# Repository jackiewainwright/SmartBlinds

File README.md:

# SmartBlinds
A senior design project that has a mobile application that sends user preferences (time, light, temp) to a micro controller system. The micro controller system tells the blinds whether to go up or down based off input from the sensor subsystem. The micro controller controls the motors which raises blinds up/down and opens slats.

# Motors
File descriptions:
- motorhw: is an Eagle project that contains the PCB I printed. The PCB was only half used since it was printed before we switched motors. The half containing the Nano and transceiver is used, while the half containing motor drivers is unused. Pictures of the schematic and layouts are in motorhw\_schematic.png and motorhw\_layout.png. 
- hardware\_photo.jpg and switch\_photo.jpg: Pictures of the final products.
- motor\_demonstration.mov: Video of the blinds being lifted, lowered and rotated to their limits. 
- logic\_diagram.png and power\_diagram.png: Basic schematics made in Fritzing. These are kind of low-quality because I couldn't find files for every part. In the logic diagram, two jacks are shown; the top supplies 12V and the bottom supplies 5V. In the drivers, A1,A2,B1,B2 aren't connected; they each should be connected to a motor. In the power diagram, imagine the battery is a Li-Ion, replace the TP4056 with a TP5410, imagine it's on a protoboard instead of breadboard. 
- keiths\_program.ino: Program used by Keith on the nano. 
- my\_program.ino: Program used by me to develop and test the motor subsystem.
- additional_validation.pdf: Validation that I didn't put in the report. My bad

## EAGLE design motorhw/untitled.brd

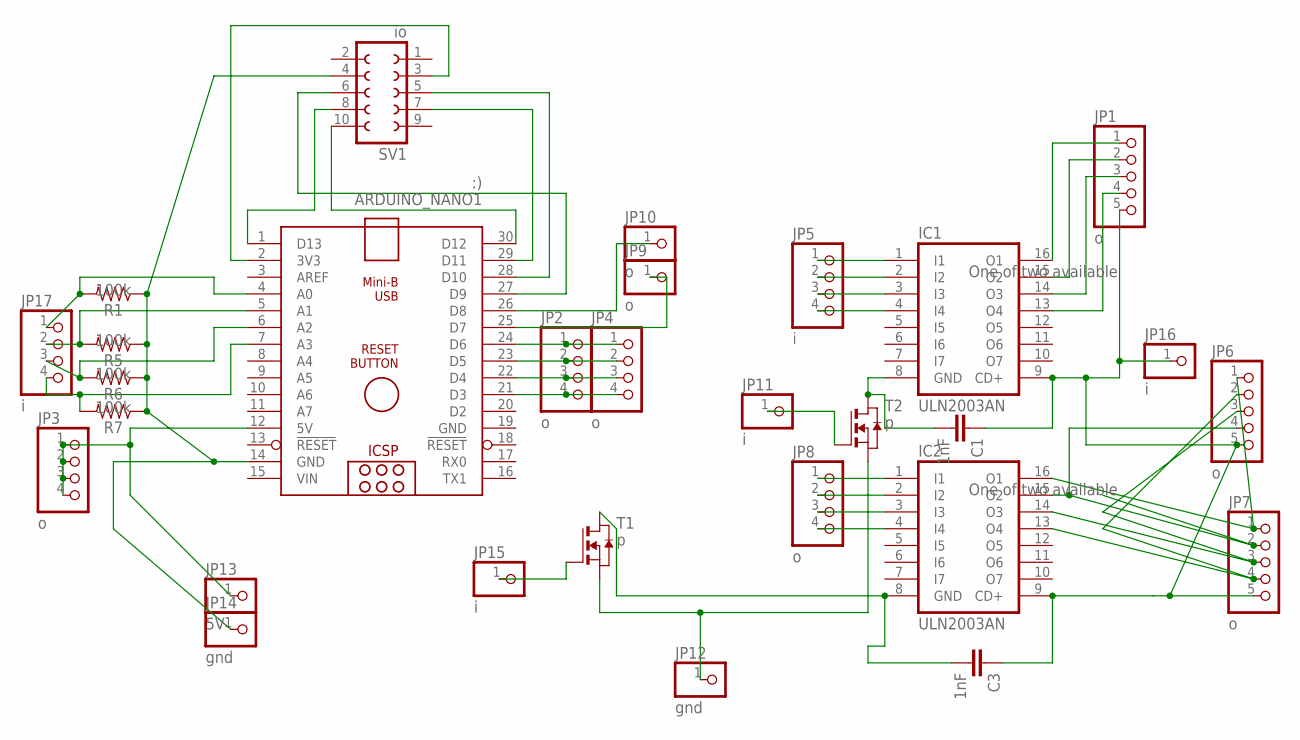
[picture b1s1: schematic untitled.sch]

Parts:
ARDUINO_NANO1: :); ARDUINO_NANO
C1, C3: 1nF; 0603
IC1, IC2: ULN2003AN; DIL16
JP1, JP6, JP7: o; 1X05
JP2, JP3, JP4, JP8: o; 1X04
JP5, JP17: i; 1X04
JP9, JP10: o; 1X01
JP11, JP15, JP16: i; 1X01
JP12, JP14: gnd; 1X01
JP13: 5V; 1X01
R1, R5, R6, R7: 100k; 0603
SV1: io; FE05-2
T1, T2: p; SOT89

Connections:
3V3: ARDUINO_NANO1.1 (D13), SV1.8
GND: ARDUINO_NANO1.19 (GND)
GND1: ARDUINO_NANO1.14 (GND), JP14.1, R1.1, R5.1, R6.1, R7.1, SV1.4
GND2: JP12.1, T1.3 (S), T2.3 (S)
LONGTHINGY: IC2.15 (O2), JP6.4, JP7.2
unnamed: ARDUINO_NANO1.4 (A0), JP17.1, R1.2
unnamed: ARDUINO_NANO1.21 (D3), JP2.4, JP4.4
unnamed: ARDUINO_NANO1.30 (D12), SV1.10
unnamed: IC2.16 (O1), JP6.1, JP7.1
unnamed: IC2.14 (O3), JP6.3, JP7.3
unnamed: IC2.13 (O4), JP6.2, JP7.4
unnamed: IC1.16 (O1), JP1.1
unnamed: IC1.15 (O2), JP1.2
unnamed: IC1.14 (O3), JP1.3
unnamed: IC1.13 (O4), JP1.4
unnamed: ARDUINO_NANO1.22 (D4), JP2.3, JP4.3
unnamed: ARDUINO_NANO1.25 (D7), JP9.1
unnamed: ARDUINO_NANO1.23 (D5), JP2.2, JP4.2
unnamed: ARDUINO_NANO1.29 (D11), SV1.7
unnamed: ARDUINO_NANO1.28 (D10), SV1.5
unnamed: ARDUINO_NANO1.27 (D9), SV1.6
unnamed: ARDUINO_NANO1.24 (D6), JP2.1, JP4.1
unnamed: ARDUINO_NANO1.2 (3V3), SV1.3
unnamed: IC1.1 (I1), JP5.1
unnamed: IC1.2 (I2), JP5.2
unnamed: IC1.3 (I3), JP5.3
unnamed: IC1.4 (I4), JP5.4
unnamed: IC2.1 (I1), JP8.1
unnamed: IC2.2 (I2), JP8.2
unnamed: IC2.3 (I3), JP8.3
unnamed: IC2.4 (I4), JP8.4
unnamed: ARDUINO_NANO1.26 (D8), JP10.1
unnamed: JP11.1, T2.1 (G)
unnamed: JP15.1, T1.1 (G)
unnamed: ARDUINO_NANO1.5 (A1), JP17.2, R5.2
unnamed: ARDUINO_NANO1.6 (A2), JP17.3, R6.2
unnamed: ARDUINO_NANO1.7 (A3), JP17.4, R7.2
ULN1GND: C1.2, IC1.8 (GND), T2.2 (D), T2.2@1 (D)
ULN2GND: C3.2, IC2.8 (GND), T1.2 (D), T1.2@1 (D)
VCC1: ARDUINO_NANO1.12 (5V), JP3.1, JP3.2, JP3.3, JP3.4, JP13.1
VCC2: C1.1, C3.1, IC1.9 (CD+), IC2.9 (CD+), JP1.5, JP6.5, JP7.5, JP16.1
VIN: ARDUINO_NANO1.15 (VIN)

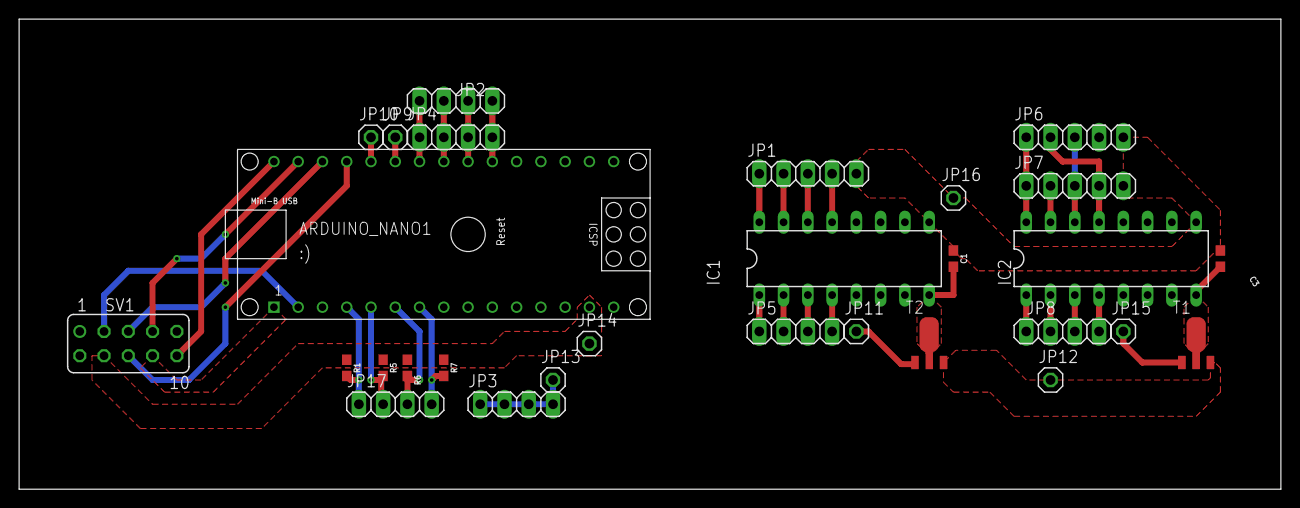
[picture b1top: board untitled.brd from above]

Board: 2 copper layers, 132.1 x 49.2 mm, 29 parts (0 on the bottom side), 40 nets.

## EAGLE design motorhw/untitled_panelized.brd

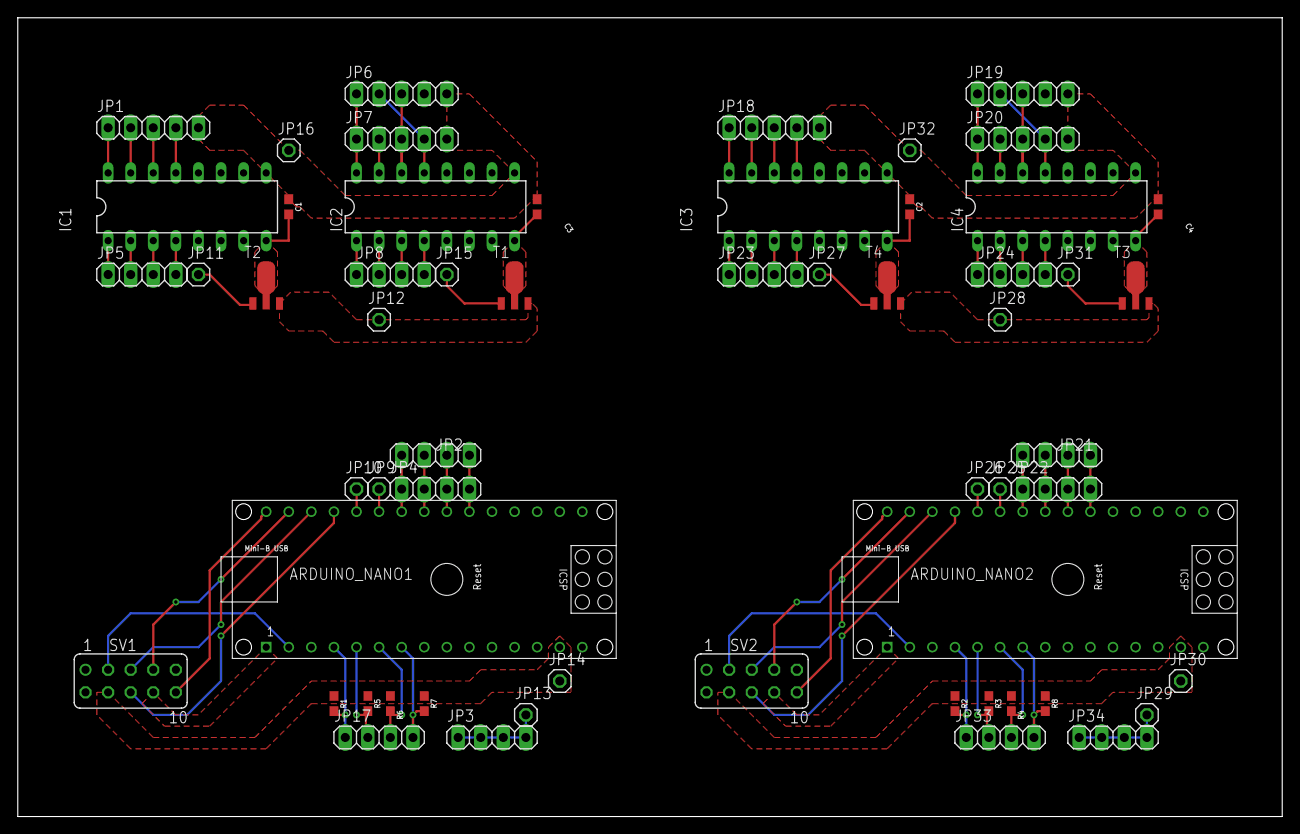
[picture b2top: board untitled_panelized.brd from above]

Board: 2 copper layers, 142.2 x 89.8 mm, 58 parts (0 on the bottom side), 80 nets.

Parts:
ARDUINO_NANO1, ARDUINO_NANO2: ARDUINO_NANO
C1, C2, C3, C4: 1nF; 0603
IC1, IC2, IC3, IC4: ULN2003AN; DIL16
JP1, JP6, JP7, JP18, JP19, JP20: 1X05
JP2, JP3, JP4, JP5, JP8, JP17, JP21, JP22, JP23, JP24, JP33, JP34: 1X04
JP9, JP10, JP11, JP12, JP13, JP14, JP15, JP16, JP25, JP26, JP27, JP28, JP29, JP30, JP31, JP32: 1X01
R1, R2, R3, R4, R5, R6, R7, R8: 100k; 0603
SV1, SV2: FE05-2
T1, T2, T3, T4: SOT89

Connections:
3V1: ARDUINO_NANO2.1, SV2.8
3V3: ARDUINO_NANO1.1, SV1.8
GND1: ARDUINO_NANO1.14, JP14.1, R1.1, R5.1, R6.1, R7.1, SV1.4
GND2: JP12.1, T1.3, T2.3
GND4: ARDUINO_NANO2.14, JP30.1, R2.1, R3.1, R4.1, R8.1, SV2.4
GND5: JP28.1, T3.3, T4.3
LONGTHINGY: IC2.15, JP6.4, JP7.2
LONGTHINGY1: IC4.15, JP19.4, JP20.2
unnamed: ARDUINO_NANO1.4, JP17.1, R1.2
unnamed: ARDUINO_NANO2.4, JP33.1, R2.2
unnamed: ARDUINO_NANO1.21, JP2.4, JP4.4
unnamed: ARDUINO_NANO1.30, SV1.10
unnamed: IC4.16, JP19.1, JP20.1
unnamed: IC2.16, JP6.1, JP7.1
unnamed: IC4.14, JP19.3, JP20.3
unnamed: IC2.14, JP6.3, JP7.3
unnamed: IC2.13, JP6.2, JP7.4
unnamed: IC4.13, JP19.2, JP20.4
unnamed: IC1.16, JP1.1
unnamed: IC1.15, JP1.2
unnamed: IC1.14, JP1.3
unnamed: IC1.13, JP1.4
unnamed: ARDUINO_NANO1.22, JP2.3, JP4.3
unnamed: IC3.16, JP18.1
unnamed: ARDUINO_NANO1.25, JP9.1
unnamed: ARDUINO_NANO1.23, JP2.2, JP4.2
unnamed: IC3.15, JP18.2
unnamed: IC3.14, JP18.3
unnamed: ARDUINO_NANO1.29, SV1.7
unnamed: ARDUINO_NANO1.28, SV1.5
unnamed: ARDUINO_NANO1.27, SV1.6
unnamed: ARDUINO_NANO1.24, JP2.1, JP4.1
unnamed: ARDUINO_NANO1.2, SV1.3
unnamed: IC3.13, JP18.4
unnamed: IC1.1, JP5.1
unnamed: IC1.2, JP5.2
unnamed: IC1.3, JP5.3
unnamed: IC1.4, JP5.4
unnamed: IC2.1, JP8.1
unnamed: IC2.2, JP8.2
unnamed: IC2.3, JP8.3
unnamed: IC2.4, JP8.4
unnamed: ARDUINO_NANO1.26, JP10.1
unnamed: JP11.1, T2.1
unnamed: JP15.1, T1.1
unnamed: ARDUINO_NANO2.30, SV2.10
unnamed: ARDUINO_NANO1.5, JP17.2, R5.2
unnamed: ARDUINO_NANO1.6, JP17.3, R6.2
unnamed: ARDUINO_NANO1.7, JP17.4, R7.2
unnamed: ARDUINO_NANO2.29, SV2.7
unnamed: ARDUINO_NANO2.28, SV2.5
unnamed: ARDUINO_NANO2.27, SV2.6
unnamed: ARDUINO_NANO2.2, SV2.3
unnamed: ARDUINO_NANO2.21, JP21.4, JP22.4
unnamed: ARDUINO_NANO2.22, JP21.3, JP22.3
unnamed: ARDUINO_NANO2.23, JP21.2, JP22.2
unnamed: ARDUINO_NANO2.24, JP21.1, JP22.1
unnamed: IC3.1, JP23.1
unnamed: IC3.2, JP23.2
unnamed: IC3.3, JP23.3
unnamed: IC3.4, JP23.4
unnamed: IC4.1, JP24.1
unnamed: IC4.2, JP24.2
unnamed: IC4.3, JP24.3
unnamed: IC4.4, JP24.4
unnamed: ARDUINO_NANO2.25, JP25.1
unnamed: ARDUINO_NANO2.26, JP26.1
unnamed: JP27.1, T4.1
unnamed: JP31.1, T3.1
unnamed: ARDUINO_NANO2.5, JP33.2, R3.2
unnamed: ARDUINO_NANO2.6, JP33.3, R4.2
unnamed: ARDUINO_NANO2.7, JP33.4, R8.2
ULN1GND: C1.2, IC1.8, T2.2, T2.2@1
ULN1GND1: C2.2, IC3.8, T4.2, T4.2@1
ULN2GND: C3.2, IC2.8, T1.2, T1.2@1
ULN2GND1: C4.2, IC4.8, T3.2, T3.2@1
VCC1: ARDUINO_NANO1.12, JP3.1, JP3.2, JP3.3, JP3.4, JP13.1
VCC2: C1.1, C3.1, IC1.9, IC2.9, JP1.5, JP6.5, JP7.5, JP16.1
VCC3: C2.1, C4.1, IC3.9, IC4.9, JP18.5, JP19.5, JP20.5, JP32.1
VCC4: ARDUINO_NANO2.12, JP29.1, JP34.1, JP34.2, JP34.3, JP34.4

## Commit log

2019-09-11 Create Mobile Application connection update
2019-09-25 Update Mobile Application connection update
2019-10-01 test
2019-10-01 First push of updates
2019-10-01 Fixed markdown formatting
2019-10-07 Create Activity Log
2019-10-14 Create ESP32 source code
2019-11-04 Another push finally
2019-11-06 Update Activity Log
2019-11-07 Adding program used to test, ft. comments to describe operation of motors
2019-11-09 Updated test program and comments. Simplified pins, slight modification of operation
2019-11-21 pushing in-progress version of program Keith worked on on my computer
2019-11-21 adding video of it working
2019-11-26 Updates and Keith's motor program
2019-12-06 adding various files
2019-12-06 fixing markdown again
2019-12-07 Adding validation that wasn't in the report

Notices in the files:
parts and their libraries:
SparkFun-Capacitors: Licensing: Creative Commons ShareAlike 4.0 International - https://creativecommons.org/licenses/by-sa/4.0
